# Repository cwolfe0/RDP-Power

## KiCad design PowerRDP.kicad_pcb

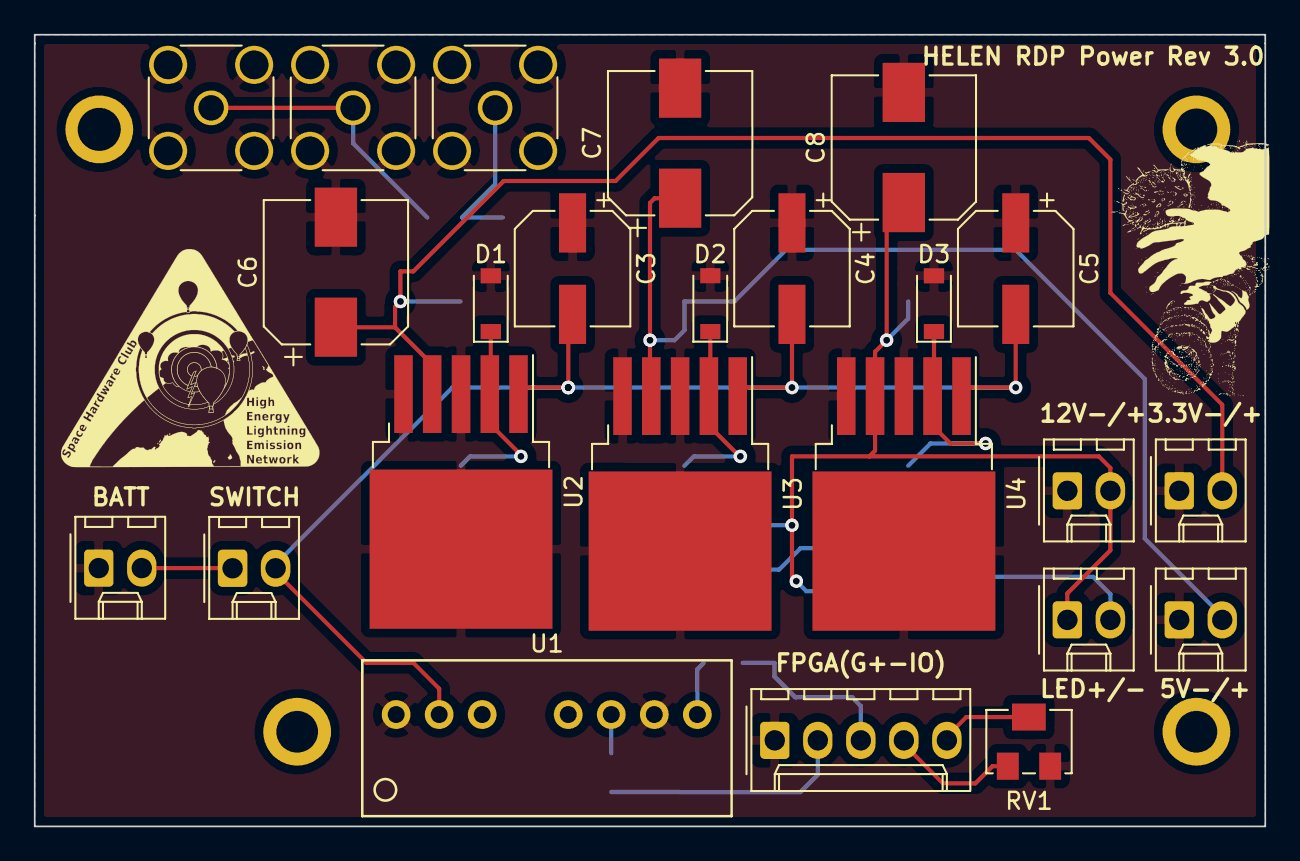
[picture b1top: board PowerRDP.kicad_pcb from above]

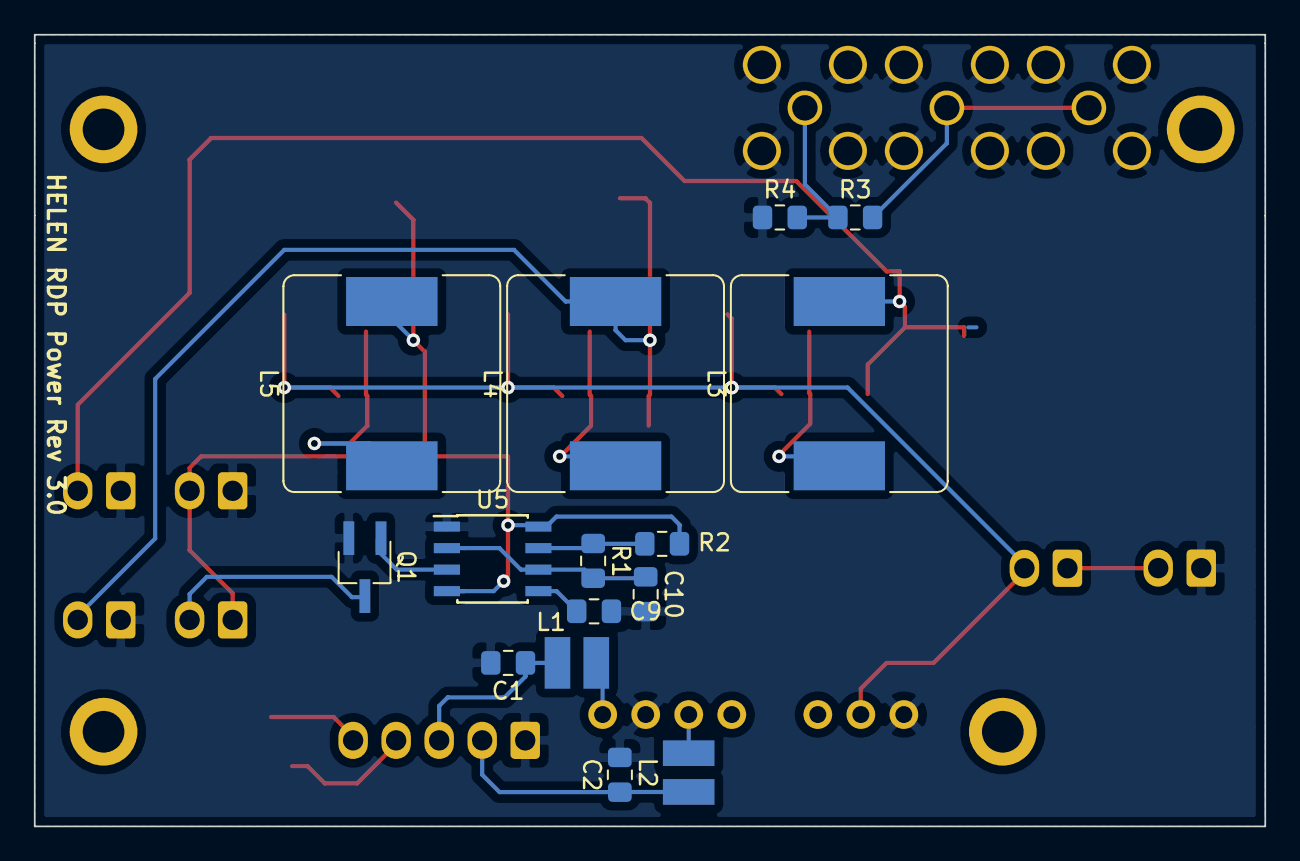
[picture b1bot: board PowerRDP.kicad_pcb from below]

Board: 2 copper layers, 72.6 x 46.7 mm, 39 parts (15 on the bottom side), 22 nets.

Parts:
C1, C2: 1 uF; C_0805_2012Metric_Pad1.15x1.40mm_HandSolder
C3, C4, C5: 100uF; CP_Elec_6.3x7.7
C6, C7, C8: 330uF; CP_Elec_8x10
C9: .01 uF; C_0805_2012Metric_Pad1.15x1.40mm_HandSolder
C10: 47 uF; C_0805_2012Metric_Pad1.15x1.40mm_HandSolder
D1, D2, D3: 1N5819; D_SOD-123
J1: Conn_01x02_Male; Molex_KK-254_AE-6410-02A_1x02_P2.54mm_Vertical
J2: Switch; Molex_KK-254_AE-6410-02A_1x02_P2.54mm_Vertical
J3, J4, J5: Conn_Coaxial; SMA_Amphenol_132134_Vertical
J6: 3.3V; Molex_KK-254_AE-6410-02A_1x02_P2.54mm_Vertical
J7: 5V; Molex_KK-254_AE-6410-02A_1x02_P2.54mm_Vertical
J8: 12V; Molex_KK-254_AE-6410-02A_1x02_P2.54mm_Vertical
J9: FAA LED; Molex_KK-254_AE-6410-02A_1x02_P2.54mm_Vertical
J10: SOCKET; Molex_KK-254_AE-6410-05A_1x05_P2.54mm_Vertical
L1, L2: 47 uH; Murata 8200
L3, L4, L5: 470uH; L_Bourns_SRR1260
Q1: NTR4003NT1G; TSOT-23_HandSoldering
R1, R2: 24k; R_0805_2012Metric_Pad1.15x1.40mm_HandSolder
R3: 1k; R_0805_2012Metric_Pad1.15x1.40mm_HandSolder
R4: 91; R_0805_2012Metric_Pad1.15x1.40mm_HandSolder
RV1: R_POT; Potentiometer_Bourns_3214W_Vertical
U1: Recom_RS3
U2: LM2575-3.3BU; TO-263-5_TabPin3
U3: LM2575-5.0BU; TO-263-5_TabPin3
U4: LM2575-12BU; TO-263-5_TabPin3
U5: TS555; SOIC-8_3.9x4.9mm_P1.27mm

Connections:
+BATT: J1.2, J2.1
/+3.3V: C6.1, J6.2, L3.2, U2.4
/+5V: C7.1, J7.2, L4.2, U3.4
/+12V: C8.1, J8.2, J9.1, L5.2, R2.1, U4.4, U5.4, U5.8
/+15V: C2.1, J10.2, L2.2
/-15V: C1.1, J10.3, L1.2
/ADC1: J3.1, J4.1, R3.2
/ADC2: J5.1, R3.1, R4.2
/C_in: J10.4, RV1.1
/C_out: J10.5, RV1.2
/FAA_GND: J9.2, Q1.3
/FAA_SIG: Q1.1, U5.3
/POWR: C3.2, C4.2, C5.2, J2.2, U1.2, U2.1, U3.1, U4.1
/THR: C10.1, R1.2, U5.2, U5.6
GND: C1.2, C2.2, C3.1, C4.1, C5.1, C6.2, C7.2, C8.2, C9.2, C10.2, D1.2, D2.2, D3.2, J1.1, J3.2, J4.2, J5.2, J6.1, J7.1, J8.1, J10.1, Q1.2, R4.1, RV1.3, U1.1, U1.7, U2.3, U2.5, U3.3, U3.5, U4.3, U4.5, U5.1
unnamed: C9.1, U5.5
unnamed: D1.1, L3.1, U2.2
unnamed: D2.1, L4.1, U3.2
unnamed: D3.1, L5.1, U4.2
unnamed: L1.1, U1.8
unnamed: L2.1, U1.6
unnamed: R1.1, R2.2, U5.7

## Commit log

2018-09-27 create PCB layout and GERBERs
2018-09-27 cleanup directories
2018-09-27 add render of board from kicad
2018-09-27 add dimensions on PCB
2018-09-27 Add pole descriptions on bottom silkscreen of +/-15V output
2018-10-10 remove old +/-15V add new (kicad files broken)
2018-10-16 Add power filtering to all regulators, correct +/-15V regulator
2018-10-18 update Gerbers
2018-10-25 Re-add drill holes
2018-10-25 Actually save the board this time to add mounting holes
2018-11-02 Slight fixes
2019-01-09 Add TODO file with information about stuff I need to fix
2019-01-10 Correct 15V regulator footprint, add potentiometer for socket gain control
2019-01-10 Increment revison
2019-01-10 Update render
2019-02-02 Fix 15V regulator, add blinking FAA LEDs
2019-02-02 Add silkscreen labels to connectors
2019-02-04 Remake power board with updated single-output regulators. PCB entirely redesigned
2019-02-04 Update diodes to something I can buy
2019-02-04 Fix capcaitors and inductors and expand board to sustain girth of new components.
2019-02-06 Add op amps and SMA connectors for socket voltage reduction
2019-02-16 Change R3 to through-hole for easier changes of amplification
2019-02-22 Fix opamps
2019-02-22 Fix opamps by adding -V supply
2019-02-22 Fix silkscreen overlaps
2019-04-08 Update 555 timer resistor value to new 50% duty cycle
2019-08-14 Update to rev3: fix 1/12 gain, simplify naming, general cleanup
